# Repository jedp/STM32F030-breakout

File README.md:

# STM32F030 Breakout board

- 16MHz HSE
- 32k LSE
- USB C connector (power only - no USB on the F030)
- Both 3V3 and 3V3A
- 4-layer board

Dimensions: 1.3 x 2.55 in

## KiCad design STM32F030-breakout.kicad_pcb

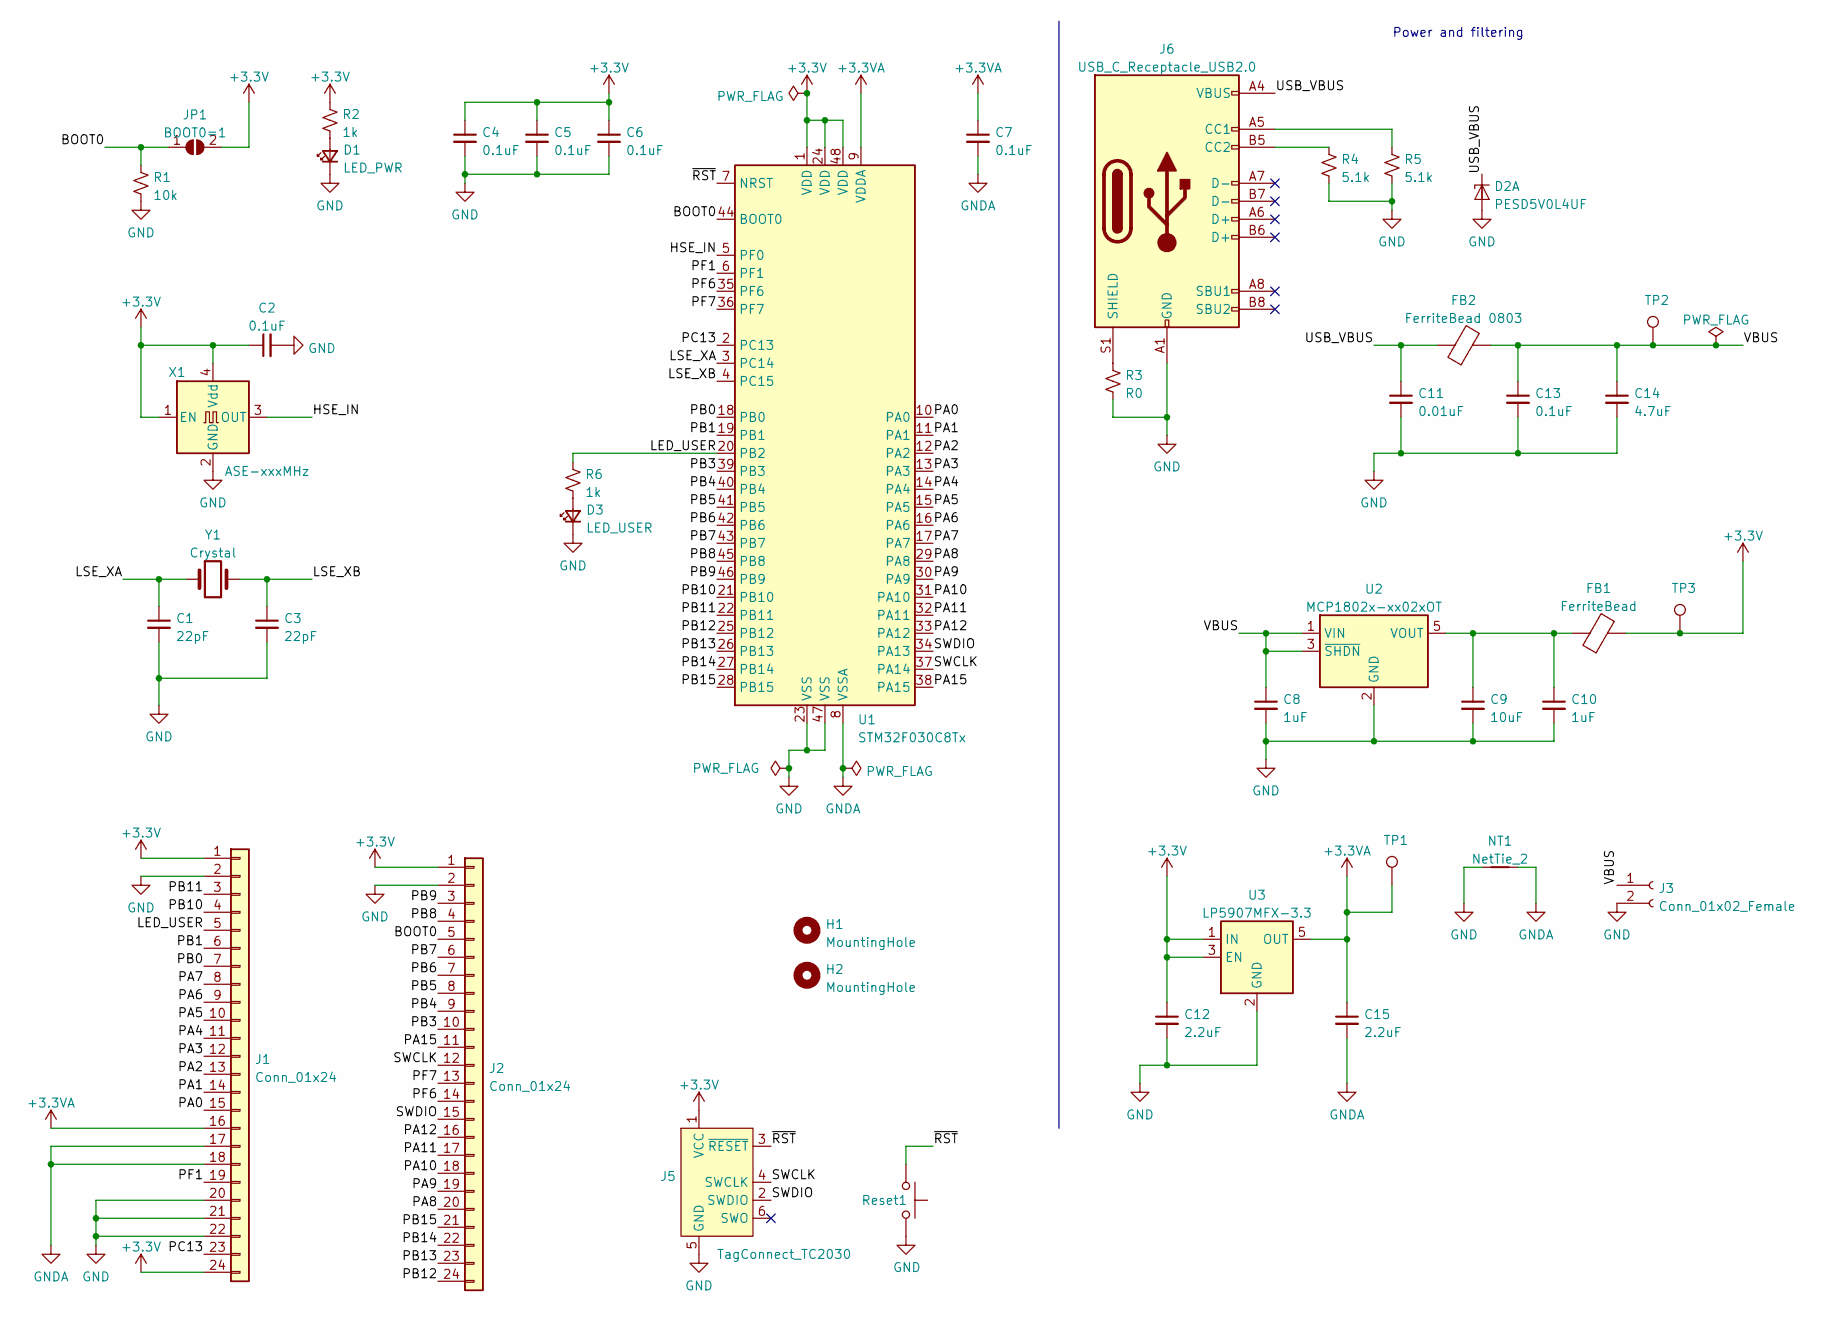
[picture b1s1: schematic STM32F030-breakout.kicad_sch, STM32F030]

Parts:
C1, C3: 22pF; C_0603_1608Metric
C2, C4, C5, C6, C7: 0.1uF; C_0603_1608Metric
C8, C10: 1uF; C_0603_1608Metric
C9: 10uF; C_0603_1608Metric
C11: 0.01uF; C_0603_1608Metric
C12, C15: 2.2uF; C_0603_1608Metric
C13: 0.1uF; C_0805_2012Metric
C14: 4.7uF; C_0805_2012Metric
D1: LED_PWR; LED_0603_1608Metric
D2: PESD5V0L4UF; SOT-886
D3: LED_USER; LED_0603_1608Metric
FB1: FerriteBead; L_0603_1608Metric
FB2: FerriteBead 0803; L_0805_2012Metric
H1, H2: MountingHole; MountingHole_2.2mm_M2
J1, J2: Conn_01x24; PinHeader_1x24_P2.54mm_Vertical
J3: Conn_01x02_Female; PinHeader_1x02_P2.54mm_Vertical
J5: TagConnect_TC2030; Tag-Connect_TC2030-IDC-FP_2x03_P1.27mm_Vertical
J6: USB_C_Receptacle_USB2.0; USB_C_Receptacle_GCT_USB4105-xx-A_16P_TopMnt_Horizontal
JP1: BOOT0=1; SolderJumper-2_P1.3mm_Open_TrianglePad1.0x1.5mm
NT1: NetTie_2; NetTie-2_SMD_Pad0.5mm
R1: 10k; R_0603_1608Metric
R2, R6: 1k; R_0603_1608Metric
R3: R0; R_0603_1608Metric
R4, R5: 5.1k; R_0603_1608Metric
Reset1: SW_Push; SW_SPST_B3U-1000P-B
TP1, TP2, TP3: TestPoint; TestPoint_Pad_D1.0mm
U1: STM32F030C8Tx; LQFP-48_7x7mm_P0.5mm
U2: MCP1802x-xx02xOT; SOT-23-5
U3: LP5907MFX-3.3; SOT-23-5
X1: ASE-xxxMHz; Oscillator_SMD_Abracon_ASE-4Pin_3.2x2.5mm
Y1: Crystal; Crystal_SMD_MicroCrystal_CC5V-T1A-2Pin_4.1x1.5mm

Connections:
+3.3V: C2.1, C4.1, C5.1, C6.1, C12.1, FB1.2, J1.1, J1.24, J2.1, J5.1 (VCC), JP1.2 (B), R2.1, TP3.1, U1.1 (VDD), U1.24 (VDD), U1.48 (VDD), U3.1 (IN), U3.3 (EN), X1.1 (EN), X1.4 (Vdd)
+3.3VA: C7.1, C15.1, J1.16, TP1.1, U1.9 (VDDA), U3.5 (OUT)
/BOOT0: J2.5, JP1.1 (A), R1.1, U1.44 (BOOT0)
/HSE_IN: U1.5 (PF0), X1.3 (OUT)
/LED_USER: J1.5, R6.1, U1.20 (PB2)
/LSE_XA: C1.1, U1.3 (PC14), Y1.1
/LSE_XB: C3.1, U1.4 (PC15), Y1.2
/PA0: J1.15, U1.10 (PA0)
/PA1: J1.14, U1.11 (PA1)
/PA2: J1.13, U1.12 (PA2)
/PA3: J1.12, U1.13 (PA3)
/PA4: J1.11, U1.14 (PA4)
/PA5: J1.10, U1.15 (PA5)
/PA6: J1.9, U1.16 (PA6)
/PA7: J1.8, U1.17 (PA7)
/PA8: J2.20, U1.29 (PA8)
/PA9: J2.19, U1.30 (PA9)
/PA10: J2.18, U1.31 (PA10)
/PA11: J2.17, U1.32 (PA11)
/PA12: J2.16, U1.33 (PA12)
/PA15: J2.11, U1.38 (PA15)
/PB0: J1.7, U1.18 (PB0)
/PB1: J1.6, U1.19 (PB1)
/PB3: J2.10, U1.39 (PB3)
/PB4: J2.9, U1.40 (PB4)
/PB5: J2.8, U1.41 (PB5)
/PB6: J2.7, U1.42 (PB6)
/PB7: J2.6, U1.43 (PB7)
/PB8: J2.4, U1.45 (PB8)
/PB9: J2.3, U1.46 (PB9)
/PB10: J1.4, U1.21 (PB10)
/PB11: J1.3, U1.22 (PB11)
/PB12: J2.24, U1.25 (PB12)
/PB13: J2.23, U1.26 (PB13)
/PB14: J2.22, U1.27 (PB14)
/PB15: J2.21, U1.28 (PB15)
/PC13: J1.23, U1.2 (PC13)
/PF1: J1.19, U1.6 (PF1)
/PF6: J2.14, U1.35 (PF6)
/PF7: J2.13, U1.36 (PF7)
/SWCLK: J2.12, J5.4 (SWCLK), U1.37 (PA14)
/SWDIO: J2.15, J5.2 (SWDIO), U1.34 (PA13)
/USB_VBUS: C11.1, D2.1 (K1), FB2.1, J6.A4 (VBUS), J6.A9 (VBUS), J6.B4 (VBUS), J6.B9 (VBUS)
/VBUS: C8.1, C13.1, C14.1, FB2.2, J3.1, TP2.1, U2.1 (VIN), U2.3 (~SHDN)
/~RST: J5.3 (~RESET), Reset1.1, U1.7 (NRST)
GND: C1.2, C2.2, C3.2, C4.2, C5.2, C6.2, C8.2, C9.2, C10.2, C11.2, C12.2, C13.2, C14.2, D1.1 (K), D2.2 (A), D2.5 (A), D3.1 (K), J1.2, J1.20, J1.21, J1.22, J2.2, J3.2, J5.5 (GND), J6.A1 (GND), J6.A12 (GND), J6.B1 (GND), J6.B12 (GND), NT1.1, R1.2, R3.2, R4.2, R5.2, Reset1.2, U1.23 (VSS), U1.47 (VSS), U2.2 (GND), U3.2 (GND), X1.2 (GND)
GNDA: C7.2, C15.2, J1.17, J1.18, NT1.2, U1.8 (VSSA)
unnamed: C9.1, C10.1, FB1.1, U2.5 (VOUT)
unnamed: D1.2 (A), R2.2
unnamed: D3.2 (A), R6.2
unnamed: J6.A5 (CC1), R5.1
unnamed: J6.B5 (CC2), R4.1
unnamed: J6.S1 (SHIELD), R3.1

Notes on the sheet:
Power and filtering

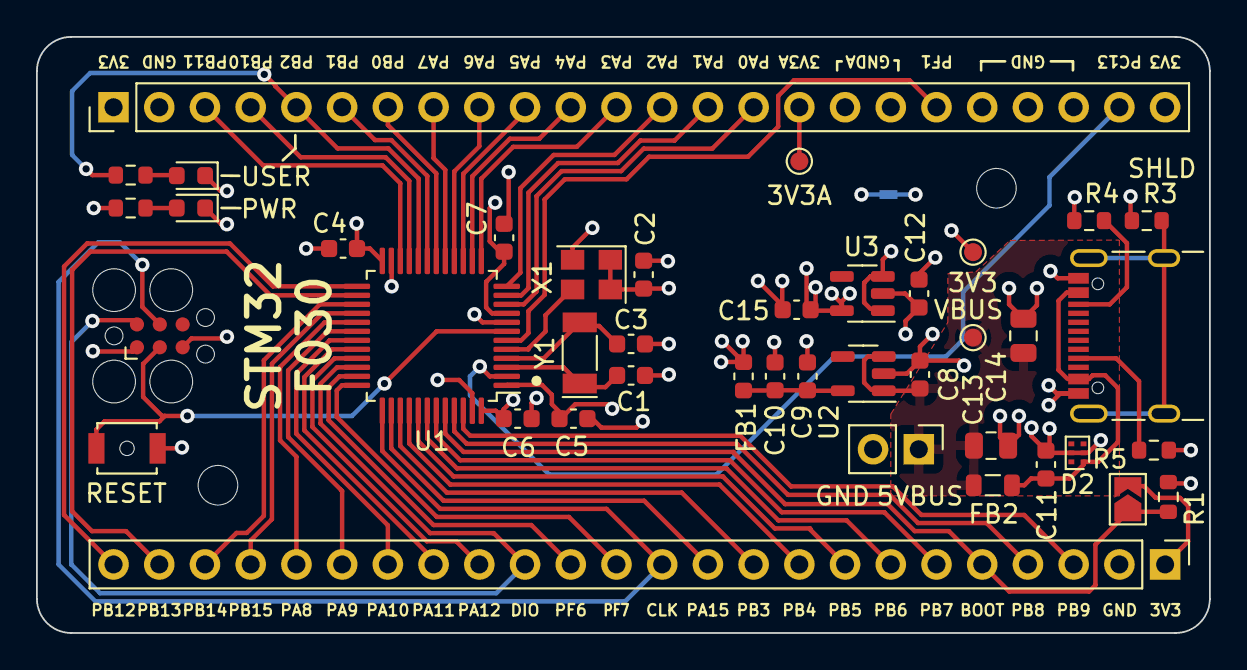
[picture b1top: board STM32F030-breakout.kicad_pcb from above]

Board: 4 copper layers, 65.2 x 33.1 mm, 44 parts (1 on the bottom side), 53 nets.

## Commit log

2023-12-27 STM32F030 breakout board
2024-01-04 Revision v1: 4-layer board; reset button
2024-01-14 Oof. SWDIO and SWCLK were on the wrong bank.
    I made the mistake of swapping out a different F030 symbol in Kicad. Turns out
    the A and B ports were swapped!
2024-01-16 Move oscillators closer
